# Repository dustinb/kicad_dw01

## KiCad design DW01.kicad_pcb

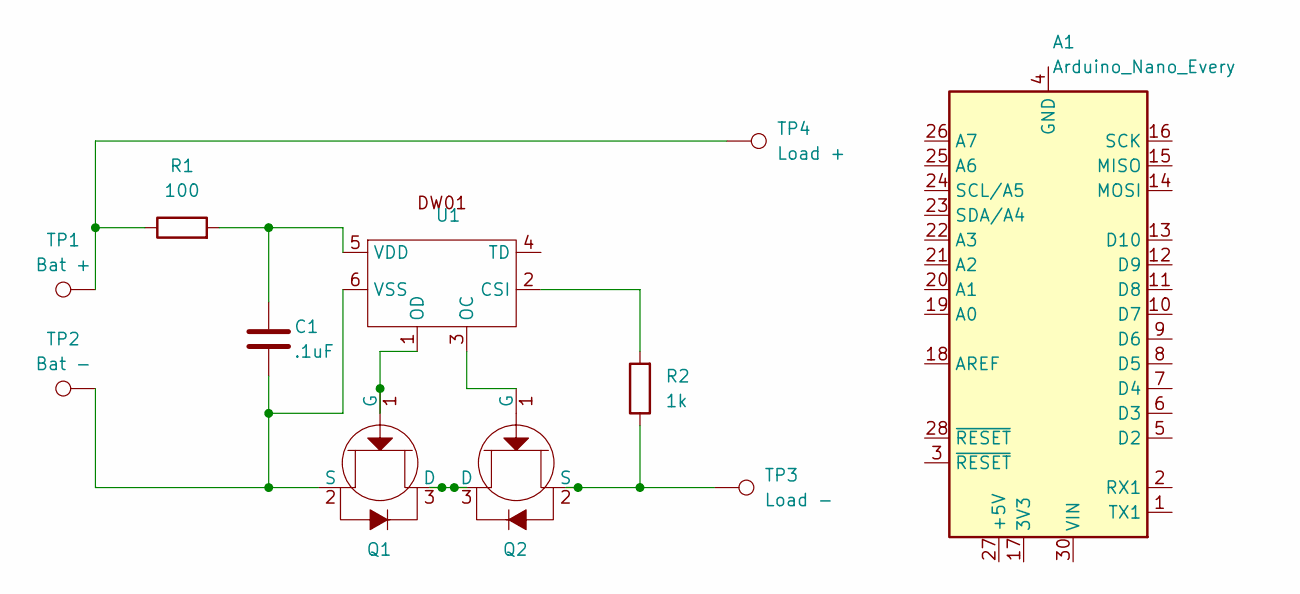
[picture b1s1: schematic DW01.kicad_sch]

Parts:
A1: Arduino_Nano_Every; Arduino_Nano
C1: .1uF; CP_Radial_D8.0mm_P3.80mm
Q1, Q2: SOT-23-3
R1: 100; R_Axial_DIN0207_L6.3mm_D2.5mm_P10.16mm_Horizontal
R2: 1k; R_Axial_DIN0207_L6.3mm_D2.5mm_P10.16mm_Horizontal
TP1: Bat +; TestPoint_Pad_D4.0mm
TP2: Bat -; TestPoint_Pad_D4.0mm
TP3: Load -; TestPoint_Pad_D4.0mm
TP4: Load +; TestPoint_Pad_D4.0mm
U1: SOT-23-6_Handsoldering

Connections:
unnamed: A1.4 (GND), A1.29 (GND)
unnamed: Q1.3 (D), Q2.3 (D)
unnamed: Q1.1 (G), U1.1 (OD)
unnamed: C1.2, Q1.2 (S), TP2.1, U1.6 (VSS)
unnamed: Q2.1 (G), U1.3 (OC)
unnamed: Q2.2 (S), R2.1, TP3.1
unnamed: R1.1, TP1.1, TP4.1
unnamed: R2.2, U1.2 (CSI)
unnamed: C1.1, R1.2, U1.5 (VDD)

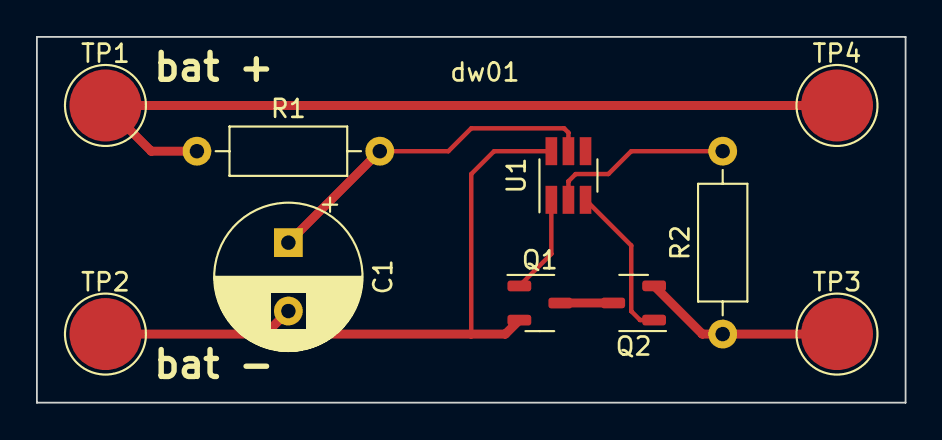
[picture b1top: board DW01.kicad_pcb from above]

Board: 2 copper layers, 48.3 x 20.3 mm, 10 parts (0 on the bottom side), 8 nets.

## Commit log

2023-09-18 init
